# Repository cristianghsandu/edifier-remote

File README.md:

# edifier-remote
An ESP32 based IR signals translator to use the LG Magic remote to control the volume on an Edifier 2.1 system

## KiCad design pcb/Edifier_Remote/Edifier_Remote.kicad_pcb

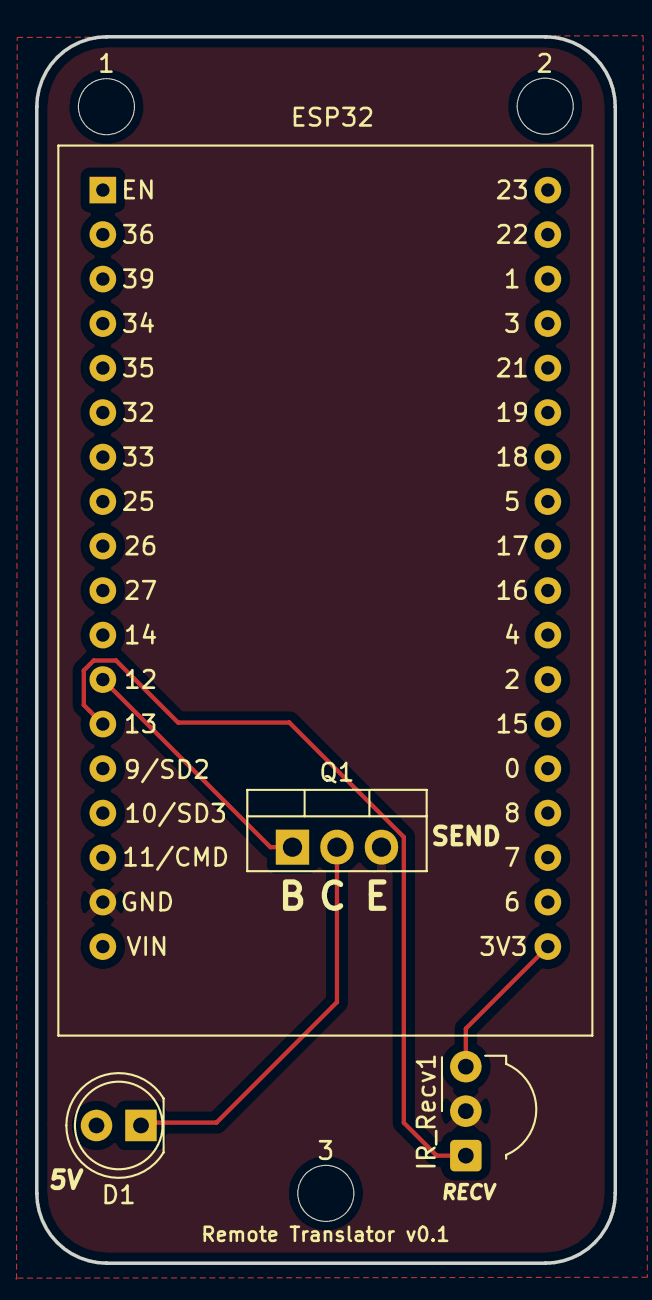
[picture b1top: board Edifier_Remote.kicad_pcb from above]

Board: 2 copper layers, 33.0 x 70.0 mm, 8 parts (0 on the bottom side), 6 nets.

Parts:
1, 2, 3: MountingHole_3.2mm_M3
CUT: BoardCutout
D1: LED; LED_D5.0mm
ESP32: ESP32_DevKit; ESP32_DevKit_36PIN
IR_Recv1: TSOP43xx; Vishay_MOLD-3Pin
Q1: Q_NPN_BCE; TO-220-3_Vertical

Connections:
/3V3: ESP32.36, IR_Recv1.3
/5V: D1.2, ESP32.18
/RECV: ESP32.13, IR_Recv1.1
/SEND: ESP32.12, Q1.1
GND: ESP32.17, IR_Recv1.2, Q1.3
unnamed: D1.1, Q1.2

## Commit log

2019-07-31 first version
2019-07-31 decerase delay
2019-07-31 attempt to implement dual core
2019-07-31 add esp32 ir remote lib
2019-07-31 raw codes
2019-08-01 initial draft
2019-08-01 minor settings
2019-08-01 add pinout
2019-08-01 barely functional
2019-08-01 convert to irrlib2
2019-08-01 make it build
2019-08-01 broken
2019-08-01 drop raw
2019-08-01 repeat held
2019-08-01 still slow
2019-08-01 slow
2019-08-02 still not fast enough
2019-08-02 cannot repeat
2019-08-02 too slow
2019-08-02 add submodule
2019-08-02 remove raw
2019-08-02 check receive
2019-08-02 repeat still sucks
2019-08-03 decode error
2019-08-03 still broken
2019-08-03 high/low values??
2019-08-03 low level protocol hacking
2019-08-03 checkpoint
2019-08-03 getting there
2019-08-03 NEC decode success?
2019-08-03 pre-cleanup
2019-08-03 getting the boys back together
2019-08-03 rename
2019-08-03 implement send
2019-08-03 fix crash
2019-08-03 main crashes
2019-08-03 threading problems
2019-08-03 fix crash in send
2019-08-03 plug edi codes
2019-08-03 send is still broken
2019-08-03 need to swap bytes!
2019-08-03 sending works I think!
2019-08-03 clean deps
2019-08-03 export repeat data
2019-08-03 extra dbg
2019-08-03 fix repeat?
2019-08-03 repeat code fixed
2019-08-03 remove debug code
2019-08-03 rm comment
2019-08-04 repeat is hard
2019-08-04 attempting to get repeats
2019-08-04 some sor of repeat
2019-08-04 timing based repeats
2019-08-05 initial PCB draft
2019-08-07 add missing file
2019-08-07 add logo
2019-08-07 arange components
2019-08-08 add filled zones
2019-08-08 replace w/ esp 32 doit
2019-08-08 update wires
2019-08-08 start designing part
2019-08-08 add initial draft of symbol
2019-08-08 added some pins
2019-08-08 added all pins
2019-08-08 update schematic
2019-08-08 finished board design
2019-08-08 change pcb label
2019-08-09 add some labels and rotate Q1
2019-08-09 swap ir led and receiver
2019-08-09 make gerber
2019-08-09 refresh gerber
2019-08-26 fixed ECB markings
2020-04-13 Export 3D model
2021-10-01 disable print with define
